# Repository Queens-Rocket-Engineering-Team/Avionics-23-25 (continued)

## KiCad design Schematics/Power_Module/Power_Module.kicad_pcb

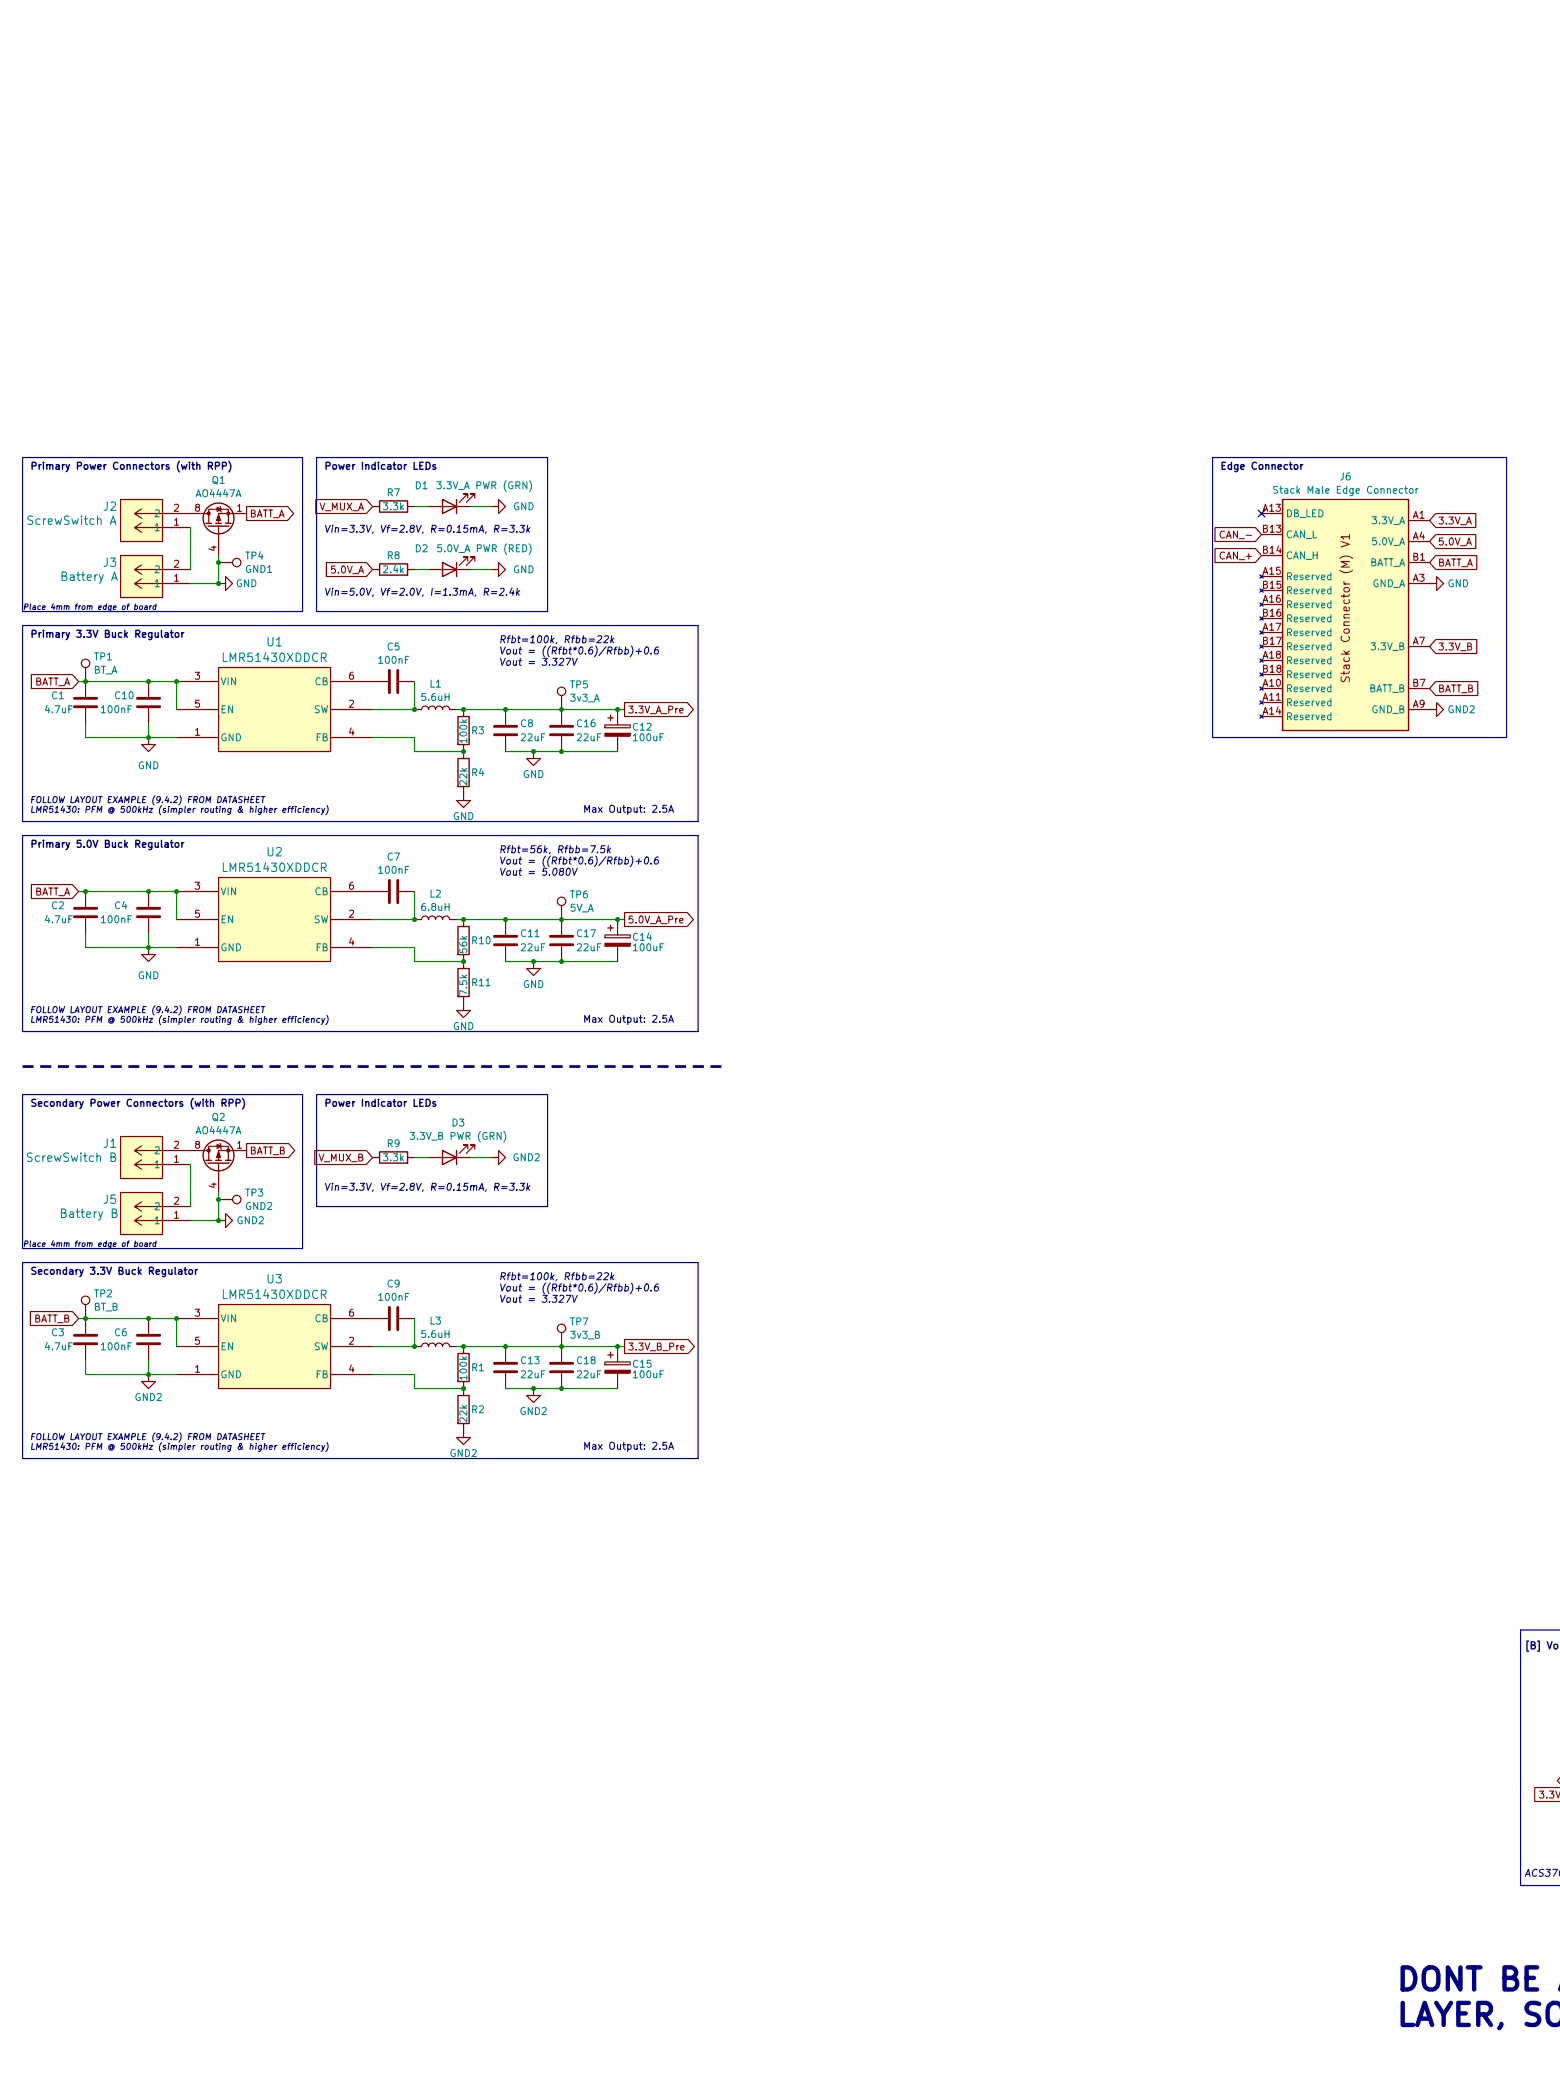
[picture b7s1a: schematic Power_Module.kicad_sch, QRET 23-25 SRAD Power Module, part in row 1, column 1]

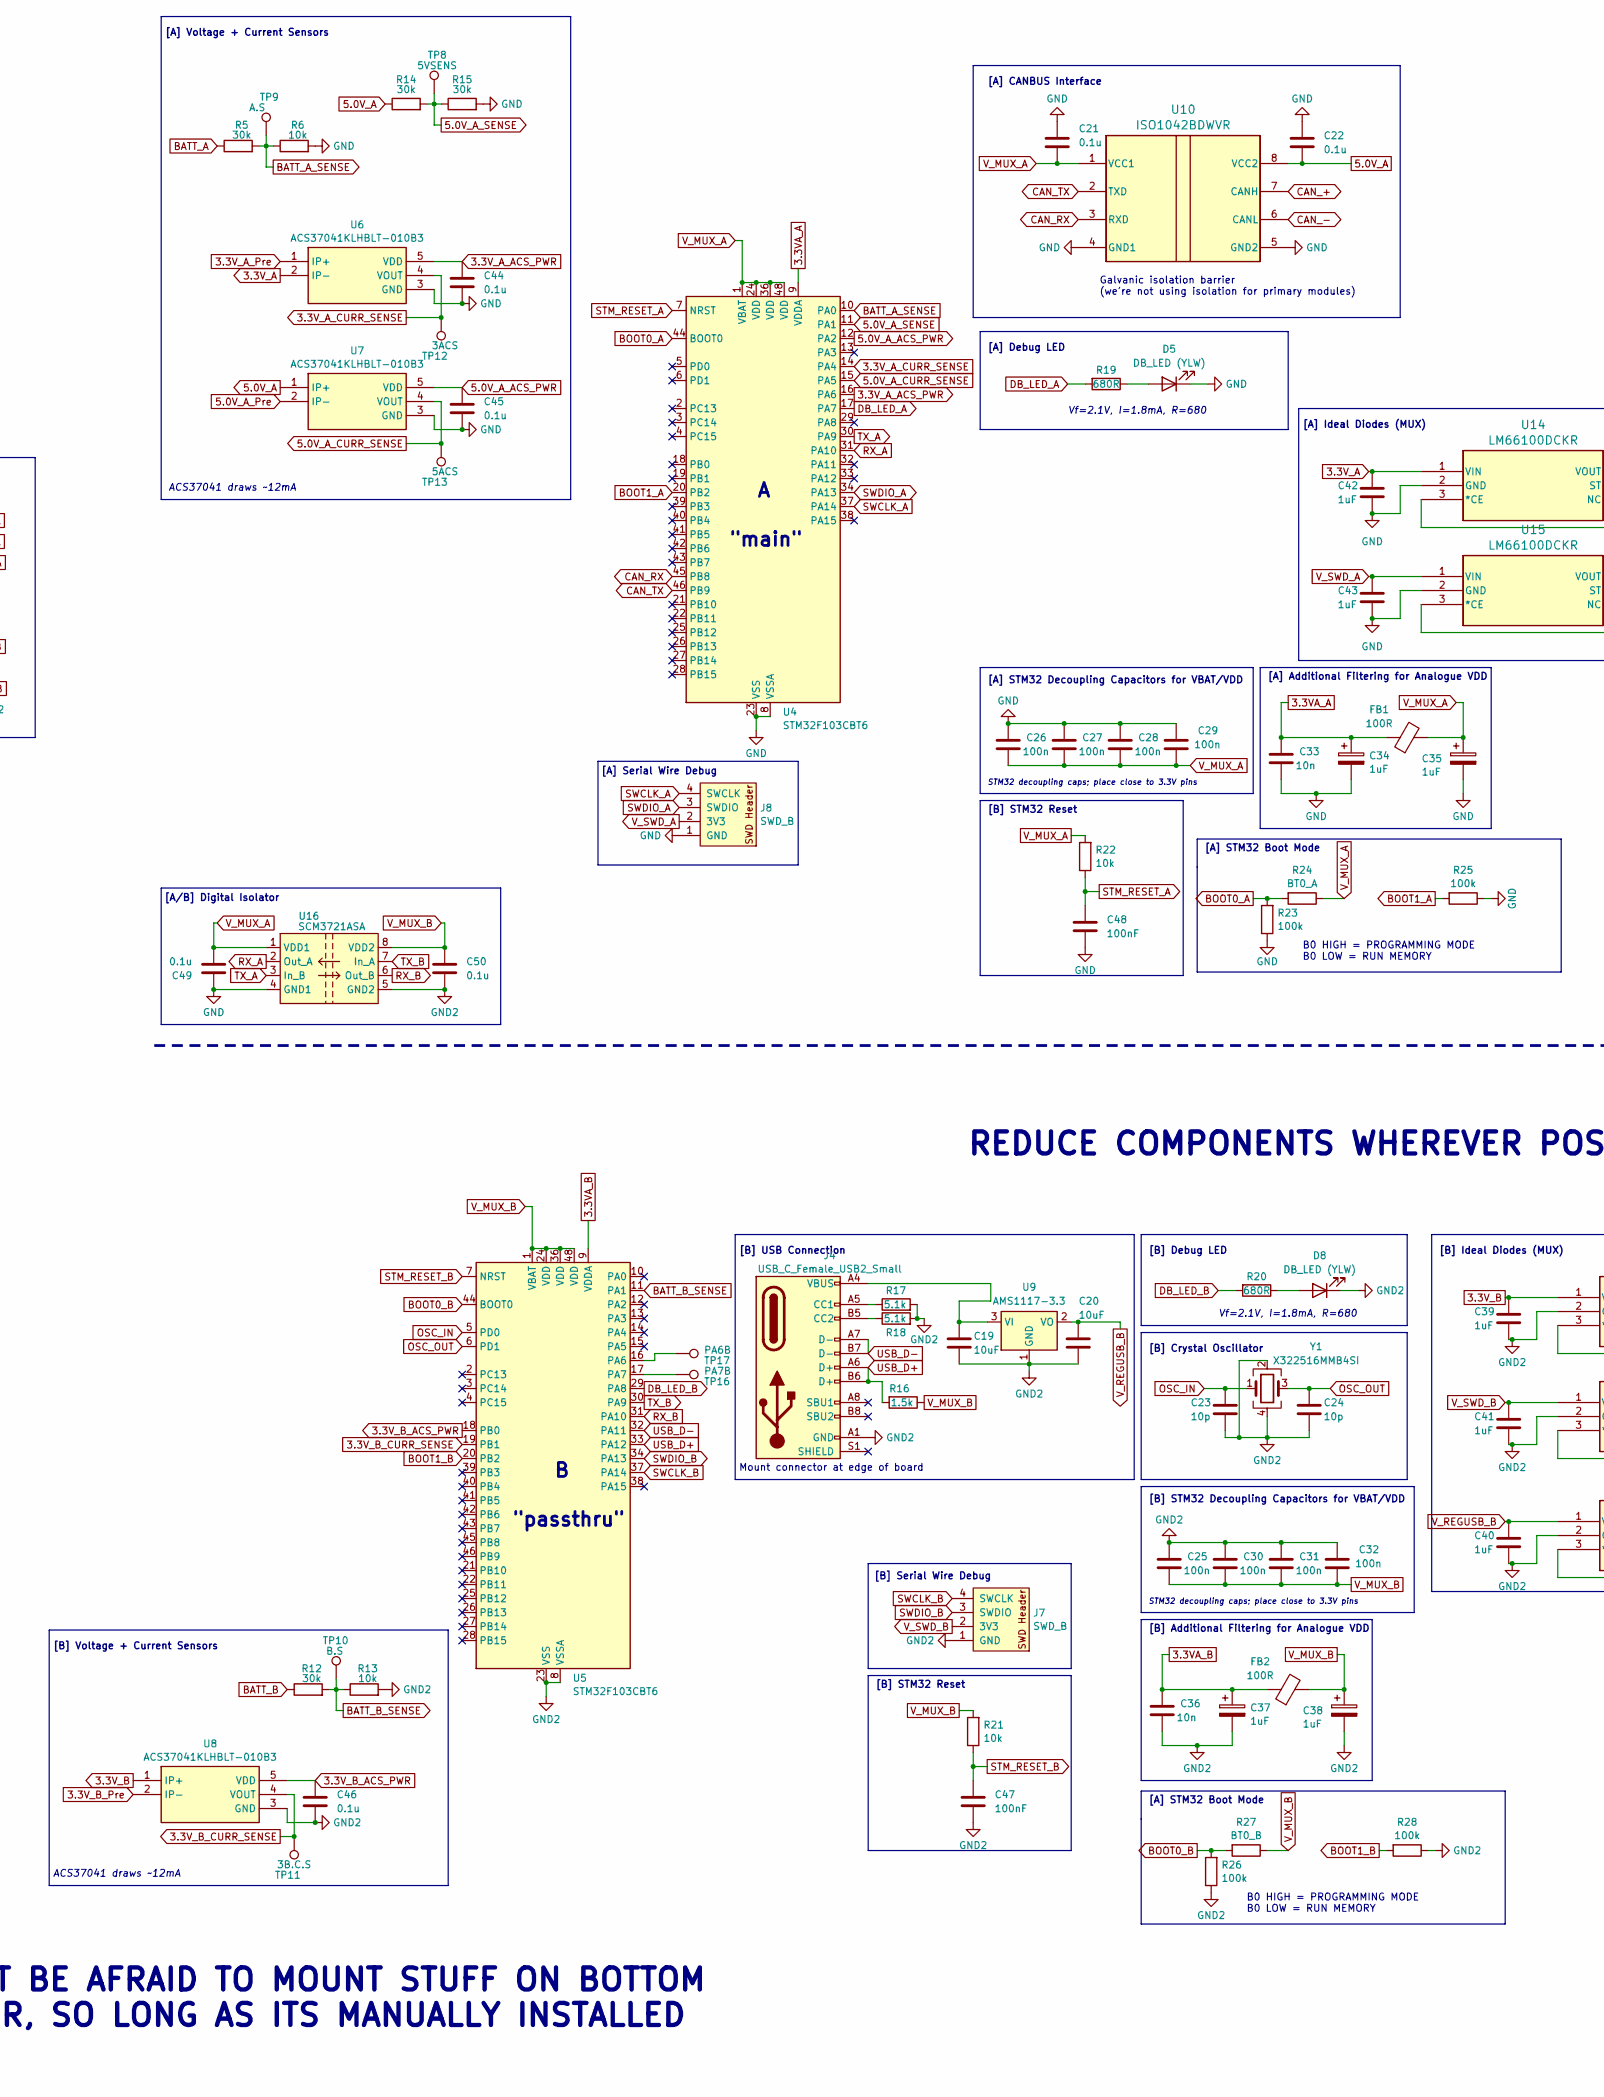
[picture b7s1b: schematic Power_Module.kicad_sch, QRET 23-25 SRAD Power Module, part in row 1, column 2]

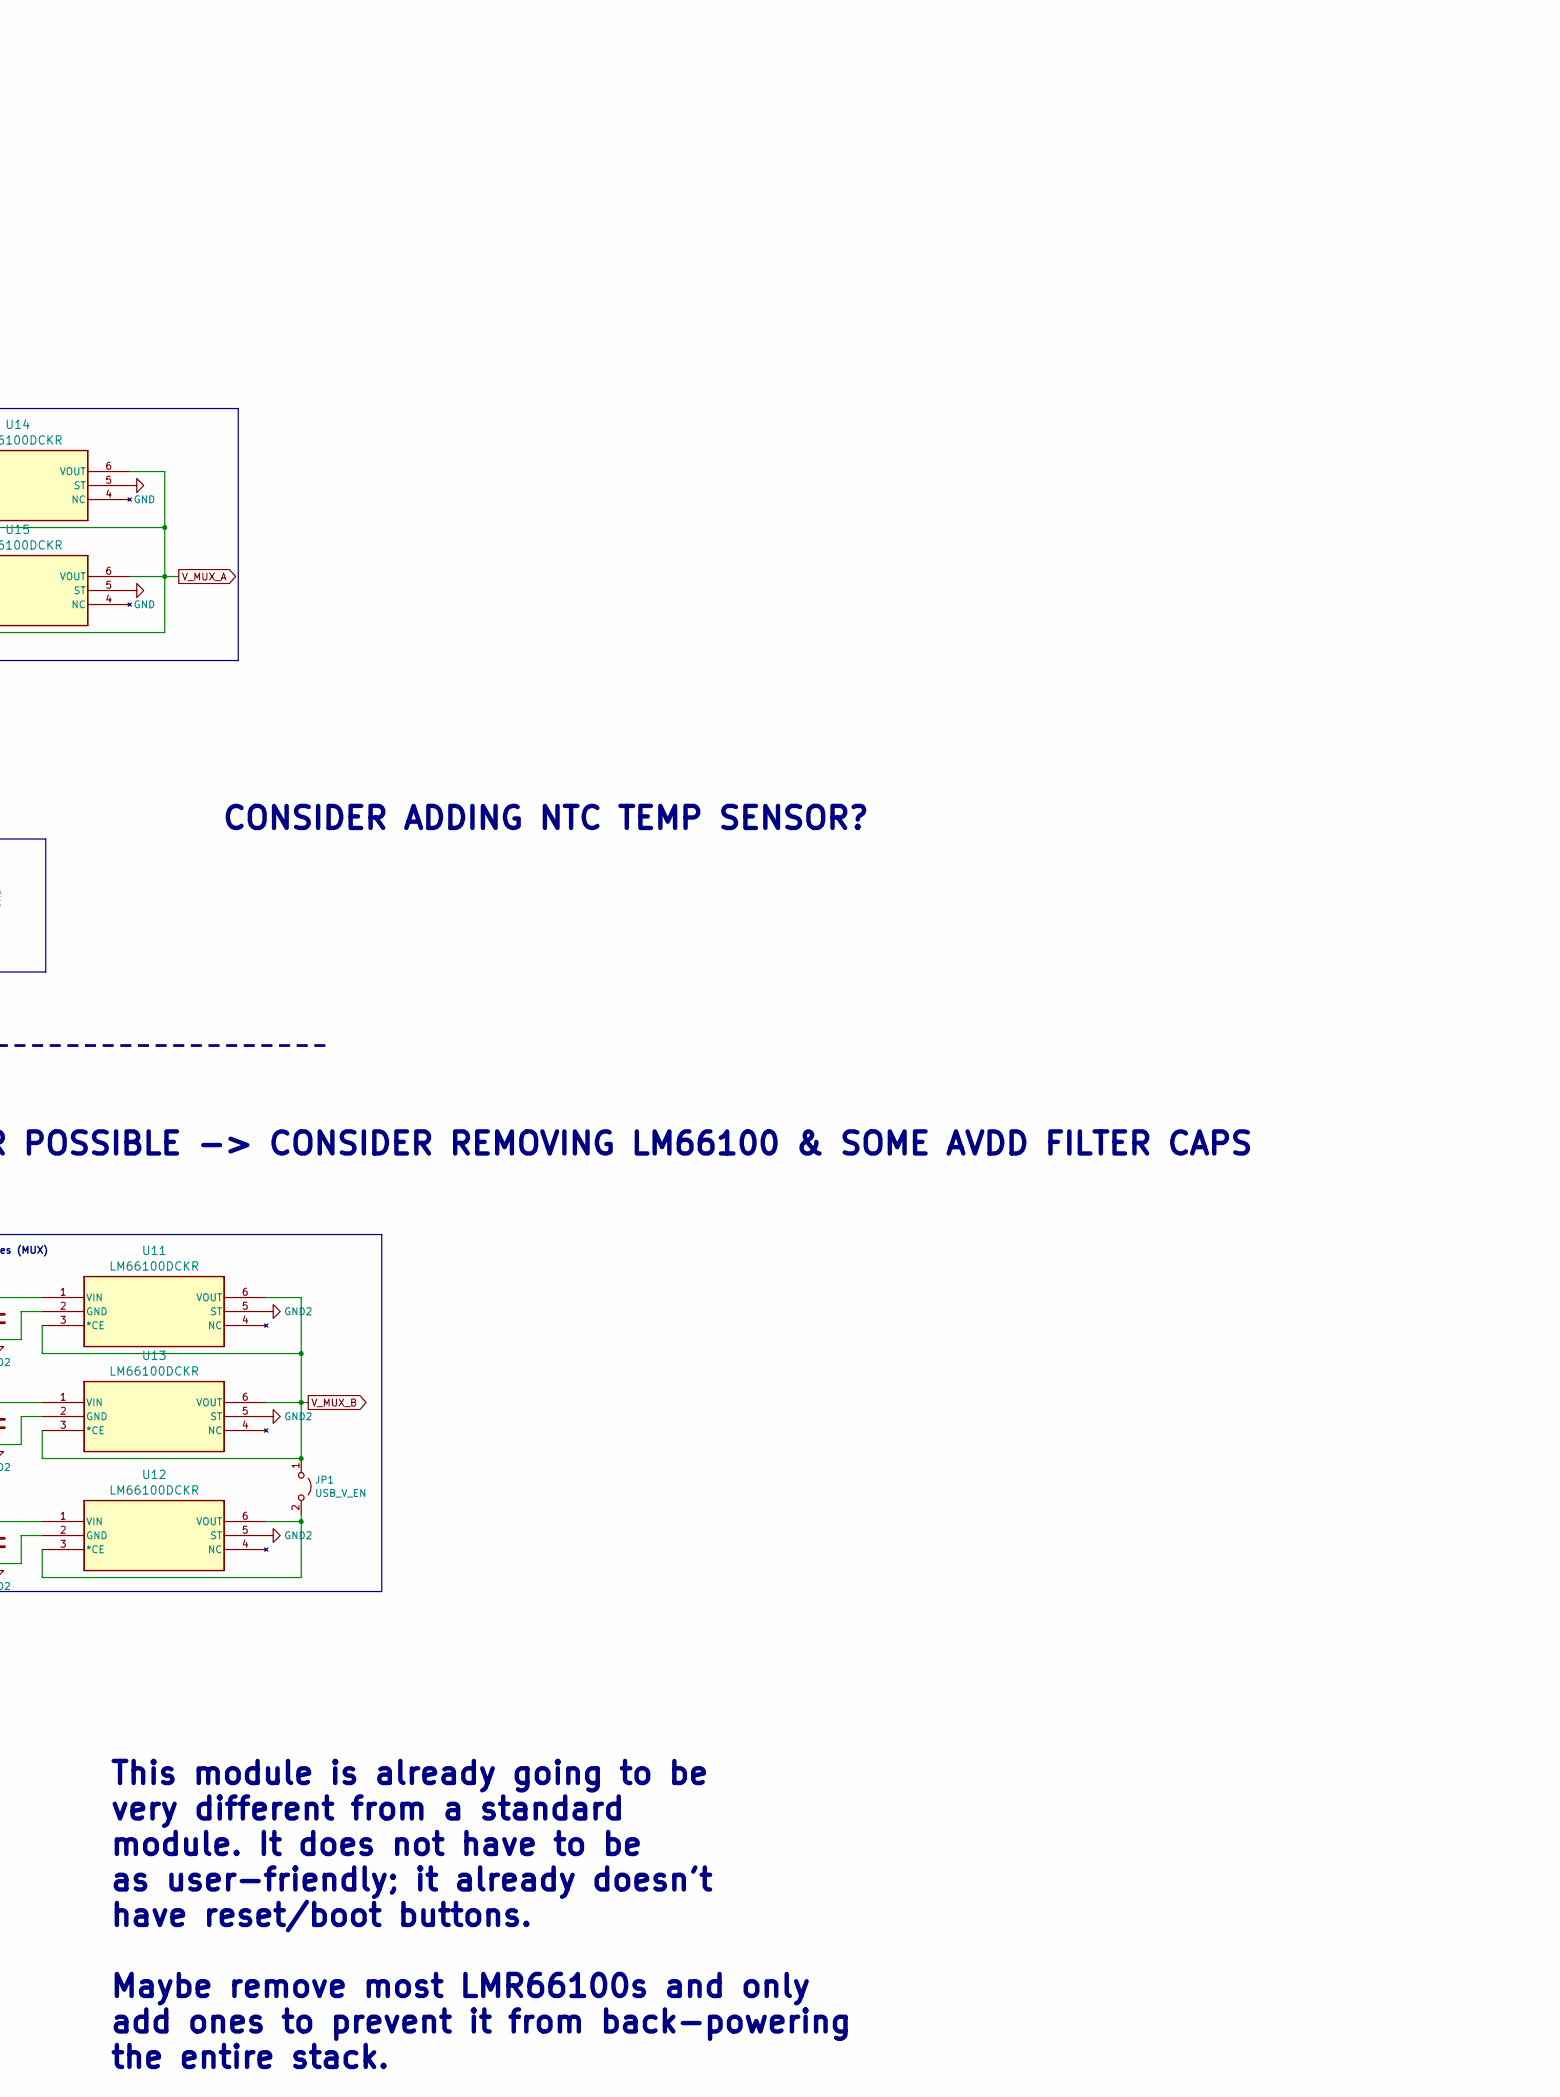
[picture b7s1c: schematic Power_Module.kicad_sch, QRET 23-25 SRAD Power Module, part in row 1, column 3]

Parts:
C1, C2, C3: 4.7uF; C_0805_2012Metric; JLCPCB C1779
C4, C5, C6, C7, C9, C10, C47, C48: 100nF; C_0603_1608Metric; JLCPCB C14663
C8, C11, C13, C16, C17, C18: 22uF; C_0805_2012Metric; JLCPCB C45783
C12, C14, C15: 100uF; CP_Elec_6.3x5.9; Digikey 732-8419-1-ND
C19, C20: 10uF; C_0603_1608Metric; JLCPCB C96446
C21, C22, C44, C45, C46: 0.1u; C_0603_1608Metric; JLCPCB C14663
C23, C24: 10p; C_0603_1608Metric; JLCPCB C1634
C25, C26, C27, C28, C29, C30, C31, C32: 100n; C_0402_1005Metric; JLCPCB C1525
C33, C36: 10n; C_0603_1608Metric; JLCPCB C57112
C34, C35, C37, C38: 1uF; C_0805_2012Metric; JLCPCB C28323
C39, C40, C41, C42, C43: 1uF; C_0603_1608Metric; JLCPCB C15849
C49, C50: 0.1u; C_0603_1608Metric_Pad1.08x0.95mm_HandSolder; JLCPCB C14663
D1: 3.3V_A PWR (GRN); LED_0805_2012Metric; JLCPCB C2297
D2: 5.0V_A PWR (RED); LED_0805_2012Metric; JLCPCB C84256
D3: 3.3V_B PWR (GRN); LED_0805_2012Metric; JLCPCB C2297
D5, D8: DB_LED (YLW); LED_0603_1608Metric; JLCPCB C72038
FB1, FB2: 100R; R_0805_2012Metric; JLCPCB C1015
J1: ScrewSwitch B; CONN_2-1445057-2_TYCO; Digikey A33212CT-ND
J2: ScrewSwitch A; CONN_2-1445057-2_TYCO; Digikey A33212CT-ND
J3: Battery A; CONN_2-1445057-2_TYCO; Digikey A33212CT-ND
J4: USB_C_Female_USB2_Small; USB_C_DB-108PWB; JLCPCB C2936184
J5: Battery B; CONN_2-1445057-2_TYCO; Digikey A33212CT-ND
J6: Stack Male Edge Connector; BUS_PCIexpress_x1
J7, J8: SWD_B; SWD_PinHeader_1x04_P2.54mm_Horizontal_SMD; Digikey 952-3233-ND
JP1: USB_V_EN; SolderJumper-2_P1.3mm_Open_RoundedPad1.0x1.5mm
L1, L3: 5.6uH; L_Bourns_SRN8040TA; Digikey SDCHA1V8040-5R6-R
L2: 6.8uH; L_Bourns_SRN8040TA; Digikey HPC 8040NC-6R8M
Q1, Q2: AO4447A; SOIC-8_3.9x4.9mm_P1.27mm; JLCPCB C125867
R1, R3, R23, R25, R26, R28: 100k; R_0603_1608Metric; JLCPCB C25803
R2, R4: 22k; R_0603_1608Metric; JLCPCB C31850
R5, R12, R14, R15: 30k; R_0603_1608Metric; JLCPCB C22984
R6, R13, R21, R22: 10k; R_0603_1608Metric; JLCPCB C25804
R7, R9: 3.3k; R_0603_1608Metric; JLCPCB C22978
R8: 2.4k; R_0603_1608Metric; JLCPCB C22940
R10: 56k; R_0603_1608Metric; JLCPCB C23206
R11: 7.5k; R_0603_1608Metric; JLCPCB C23234
R16: 1.5k; R_0603_1608Metric; JLCPCB C22843
R17, R18: 5.1k; R_0603_1608Metric; JLCPCB C23186
R19, R20: 680R; R_0603_1608Metric; JLCPCB C23228
R24: BT0_A; R_0603_1608Metric_Pad0.98x0.95mm_HandSolder
R27: BT0_B; R_0603_1608Metric_Pad0.98x0.95mm_HandSolder
TP1: BT_A; TestPoint_Pad_2.0x2.0mm
TP2: BT_B; TestPoint_Pad_2.0x2.0mm
TP3: GND2; TestPoint_Pad_2.0x2.0mm
TP4: GND1; TestPoint_Pad_2.0x2.0mm
TP5: 3v3_A; TestPoint_Pad_2.0x2.0mm
TP6: 5V_A; TestPoint_Pad_2.0x2.0mm
TP7: 3v3_B; TestPoint_Pad_2.0x2.0mm
TP8: 5VSENS; TestPoint_Pad_1.5x1.5mm
TP9: A.S; TestPoint_Pad_1.5x1.5mm
TP10: B.S; TestPoint_Pad_1.5x1.5mm
TP11: 3B.C.S; TestPoint_Pad_1.5x1.5mm
TP12: 3ACS; TestPoint_Pad_1.5x1.5mm
TP13: 5ACS; TestPoint_Pad_1.5x1.5mm
TP16: PA7B; TestPoint_Pad_1.5x1.5mm
TP17: PA6B; TestPoint_Pad_1.5x1.5mm
U1, U2, U3: LMR51430XDDCR; SOT-23-6_Handsoldering; Digikey 296-LMR51430XDDCRCT-ND
U4, U5: STM32F103CBT6; LQFP-48_7x7mm_P0.5mm; JLCPCB C8304
U6, U7, U8: ACS37041KLHBLT-010B3; APS12628LLHALTBAP_HandSolder; Digikey 620-ACS37041KLHBLT-010B3CT-ND
U9: AMS1117-3.3; SOT-223-3_TabPin2; JLCPCB C6186
U10: ISO1042BDWVR; SOIC-8 ISO1042BDWV; JLCPCB C484409
U11, U12, U13, U14, U15: LM66100DCKR; SC-70-6_Handsoldering; JLCPCB C2869734
U16: SCM3721ASA; SOIC-8_3.9x4.9mm_P1.27mm; Digikey 2725-SCM3721ASACT-ND
Y1: X322516MMB4SI; Crystal_SMD_3225-4Pin_3.2x2.5mm; JLCPCB C13738

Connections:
3.3VA_A: C33.1, C34.1, FB1.1, U4.9 (VDDA)
3.3VA_B: C36.1, C37.1, FB2.1, U5.9 (VDDA)
3.3V_A: C42.1, J6.A1 (3.3V_A), J6.A2 (3.3V_A), U6.2 (IP-), U14.1 (VIN)
3.3V_A_ACS_PWR: C44.1, U4.16 (PA6), U6.5 (VDD)
3.3V_A_CURR_SENSE: TP12.1, U4.14 (PA4), U6.4 (VOUT)
3.3V_A_Pre: C8.1, C12.1, C16.1, L1.2, R3.1, TP5.1, U6.1 (IP+)
3.3V_B: C39.1, J6.A7 (3.3V_B), J6.A8 (3.3V_B), U8.1 (IP+), U11.1 (VIN)
3.3V_B_ACS_PWR: C46.1, U5.18 (PB0), U8.5 (VDD)
3.3V_B_CURR_SENSE: TP11.1, U5.19 (PB1), U8.4 (VOUT)
3.3V_B_Pre: C13.1, C15.1, C18.1, L3.2, R1.1, TP7.1, U8.2 (IP-)
5.0V_A: C22.2, J6.A4 (5.0V_A), J6.A5 (5.0V_A), R8.1, R14.1, U7.1 (IP+), U10.8 (VCC2)
5.0V_A_ACS_PWR: C45.1, U4.12 (PA2), U7.5 (VDD)
5.0V_A_CURR_SENSE: TP13.1, U4.15 (PA5), U7.4 (VOUT)
5.0V_A_Pre: C11.1, C14.1, C17.1, L2.2, R10.1, TP6.1, U7.2 (IP-)
5.0V_A_SENSE: R14.2, R15.1, TP8.1, U4.11 (PA1)
BATT_A: C1.1, C2.1, C4.1, C10.1, J6.B1 (BATT_A), J6.B2 (BATT_A), J6.B3 (BATT_A), Q1.1 (S), Q1.2 (S), Q1.3 (S), R5.1, TP1.1, U1.3 (VIN), U1.5 (EN), U2.3 (VIN), U2.5 (EN)
BATT_A_SENSE: R5.2, R6.1, TP9.1, U4.10 (PA0)
BATT_B: C3.1, C6.1, J6.B7 (BATT_B), J6.B8 (BATT_B), J6.B9 (BATT_B), Q2.1 (S), Q2.2 (S), Q2.3 (S), R12.1, TP2.1, U3.3 (VIN), U3.5 (EN)
BATT_B_SENSE: R12.2, R13.1, TP10.1, U5.11 (PA1)
BOOT0_A: R23.2, R24.2, U4.44 (BOOT0)
BOOT0_B: R26.2, R27.2, U5.44 (BOOT0)
BOOT1_A: R25.2, U4.20 (PB2)
BOOT1_B: R28.2, U5.20 (PB2)
CAN_+: J6.B14 (CAN_H), U10.7 (CANH)
CAN_-: J6.B13 (CAN_L), U10.6 (CANL)
CAN_RX: U4.45 (PB8), U10.3 (RXD)
CAN_TX: U4.46 (PB9), U10.2 (TXD)
DB_LED_A: R19.2, U4.17 (PA7)
DB_LED_B: R20.2, U5.29 (PA8)
GND: C1.2, C2.2, C4.2, C8.2, C10.2, C11.2, C12.2, C14.2, C16.2, C17.2, C21.1, C22.1, C26.1, C27.1, C28.1, C29.1, C33.2, C34.2, C35.2, C42.2, C43.2, C44.2, C45.2, C48.2, C49.1, D1.1 (K), D2.1 (K), D5.1 (K), J3.1, J6.A3 (GND_A), J6.A6 (GND_A), J6.B4 (GND_A), J6.B5 (GND_A), J6.B6 (GND_A), J8.1 (GND), Q1.4 (G), R4.2, R6.2, R11.2, R15.2, R23.1, R25.1, TP4.1, U1.1 (GND), U2.1 (GND), U4.8 (VSSA), U4.23 (VSS), U4.35 (VSS), U4.47 (VSS), U6.3 (GND), U7.3 (GND), U10.4 (GND1), U10.5 (GND2), U14.2 (GND), U14.5 (ST), U15.2 (GND), U15.5 (ST), U16.4 (GND1)
GND2: C3.2, C6.2, C13.2, C15.2, C18.2, C19.2, C20.2, C23.2, C24.2, C25.1, C30.1, C31.1, C32.1, C36.2, C37.2, C38.2, C39.2, C40.2, C41.2, C46.2, C47.2, C50.2, D3.1 (K), D8.1 (K), J4.A1 (GND), J4.A12 (GND), J4.B1 (GND), J4.B12 (GND), J5.1, J6.A9 (GND_B), J6.A12 (GND_B), J6.B10 (GND_B), J6.B11 (GND_B), J6.B12 (GND_B), J7.1 (GND), Q2.4 (G), R2.2, R13.2, R17.2, R18.2, R26.1, R28.1, TP3.1, U3.1 (GND), U5.8 (VSSA), U5.23 (VSS), U5.35 (VSS), U5.47 (VSS), U8.3 (GND), U9.1 (GND), U11.2 (GND), U11.5 (ST), U12.2 (GND), U12.5 (ST), U13.2 (GND), U13.5 (ST), U16.5 (GND2), Y1.2, Y1.4
unnamed: D1.2 (A), R7.2
unnamed: D2.2 (A), R8.2
unnamed: D3.2 (A), R9.2
unnamed: D5.2 (A), R19.1
unnamed: D8.2 (A), R20.1
unnamed: J1.1, J5.2
unnamed: J1.2, Q2.5 (D), Q2.6 (D), Q2.7 (D), Q2.8 (D)
unnamed: J2.1, J3.2
unnamed: J2.2, Q1.5 (D), Q1.6 (D), Q1.7 (D), Q1.8 (D)
unnamed: J4.A5 (CC1), R17.1
unnamed: J4.B5 (CC2), R18.1
unnamed: JP1.2 (B), U12.3 (*CE), U12.6 (VOUT)
unnamed: C5.2, U1.6 (CB)
unnamed: R3.2, R4.1, U1.4 (FB)
unnamed: C5.1, L1.1, U1.2 (SW)
unnamed: C7.2, U2.6 (CB)
unnamed: R10.2, R11.1, U2.4 (FB)
unnamed: C7.1, L2.1, U2.2 (SW)
unnamed: C9.2, U3.6 (CB)
unnamed: R1.2, R2.1, U3.4 (FB)
unnamed: C9.1, L3.1, U3.2 (SW)
unnamed: TP17.1, U5.16 (PA6)
unnamed: TP16.1, U5.17 (PA7)
unnamed: C19.1, J4.A4 (VBUS), J4.A9 (VBUS), J4.B4 (VBUS), J4.B9 (VBUS), U9.3 (VI)
OSC_IN: C23.1, U5.5 (PD0), Y1.1
OSC_OUT: C24.1, U5.6 (PD1), Y1.3
RX_A: U4.31 (PA10), U16.2 (Out_A)
RX_B: U5.31 (PA10), U16.6 (Out_B)
STM_RESET_A: C48.1, R22.1, U4.7 (NRST)
STM_RESET_B: C47.1, R21.1, U5.7 (NRST)
SWCLK_A: J8.4 (SWCLK), U4.37 (PA14)
SWCLK_B: J7.4 (SWCLK), U5.37 (PA14)
SWDIO_A: J8.3 (SWDIO), U4.34 (PA13)
SWDIO_B: J7.3 (SWDIO), U5.34 (PA13)
TX_A: U4.30 (PA9), U16.3 (In_B)
TX_B: U5.30 (PA9), U16.7 (In_A)
USB_D+: J4.A6 (D+), J4.B6 (D+), R16.2, U5.33 (PA12)
USB_D-: J4.A7 (D-), J4.B7 (D-), U5.32 (PA11)
V_MUX_A: C21.2, C26.2, C27.2, C28.2, C29.2, C35.1, C49.2, FB1.2, R7.1, R22.2, R24.1, U4.1 (VBAT), U4.24 (VDD), U4.36 (VDD), U4.48 (VDD), U10.1 (VCC1), U14.3 (*CE), U14.6 (VOUT), U15.3 (*CE), U15.6 (VOUT), U16.1 (VDD1)
V_MUX_B: C25.2, C30.2, C31.2, C32.2, C38.1, C50.1, FB2.2, JP1.1 (A), R9.1, R16.1, R21.2, R27.1, U5.1 (VBAT), U5.24 (VDD), U5.36 (VDD), U5.48 (VDD), U11.3 (*CE), U11.6 (VOUT), U13.3 (*CE), U13.6 (VOUT), U16.8 (VDD2)
V_REGUSB_B: C20.1, C40.1, U9.2 (VO), U12.1 (VIN)
V_SWD_A: C43.1, J8.2 (3V3), U15.1 (VIN)
V_SWD_B: C41.1, J7.2 (3V3), U13.1 (VIN)

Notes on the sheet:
Place 4mm from edge of board
Max Output: 2.5A
Primary Power Connectors (with RPP)
[B] Voltage + Current Sensors
B0 HIGH = PROGRAMMING MODE B0 LOW = RUN MEMORY
STM32 decoupling caps; place close to 3.3V pins
[A] Voltage + Current Sensors
Primary 5.0V Buck Regulator
[B] Debug LED
Primary 3.3V Buck Regulator
Vf=2.1V, I=1.8mA, R=680
"main"
Galvanic isolation barrier (we're not using isolation for primary modules)
[B] Crystal Oscillator
ACS37041 draws ~12mA
[B] STM32 Reset
Secondary Power Connectors (with RPP)
Vin=3.3V, Vf=2.8V, R=0.15mA, R=3.3k
FOLLOW LAYOUT EXAMPLE (9.4.2) FROM DATASHEET LMR51430: PFM @ 500kHz (simpler routing & higher efficiency)
Rfbt=56k, Rfbb=7.5k Vout = ((Rfbt*0.6)/Rfbb)+0.6 Vout = 5.080V
Mount connector at edge of board
Power Indicator LEDs
CONSIDER ADDING NTC TEMP SENSOR?
[B] Ideal Diodes (MUX)
Vin=5.0V, Vf=2.0V, I=1.3mA, R=2.4k
[B] Serial Wire Debug
Rfbt=100k, Rfbb=22k Vout = ((Rfbt*0.6)/Rfbb)+0.6 Vout = 3.327V
[A/B] Digital Isolator
"passthru"
[A] STM32 Boot Mode
[A] CANBUS Interface
[B] Additional Filtering for Analogue VDD
REDUCE COMPONENTS WHEREVER POSSIBLE -> CONSIDER REMOVING LM66100 & SOME AVDD FILTER CAPS
This module is already going to be very different from a standard module. It does not have to be as user-friendly; it already doesn't have reset/boot buttons. Maybe remove most LMR66100s and only add ones to prevent it from back-powering the entire stack.
[B] STM32 Decoupling Capacitors for VBAT/VDD
[A] Additional Filtering for Analogue VDD
Edge Connector
[B] USB Connection
[A] Ideal Diodes (MUX)
Secondary 3.3V Buck Regulator

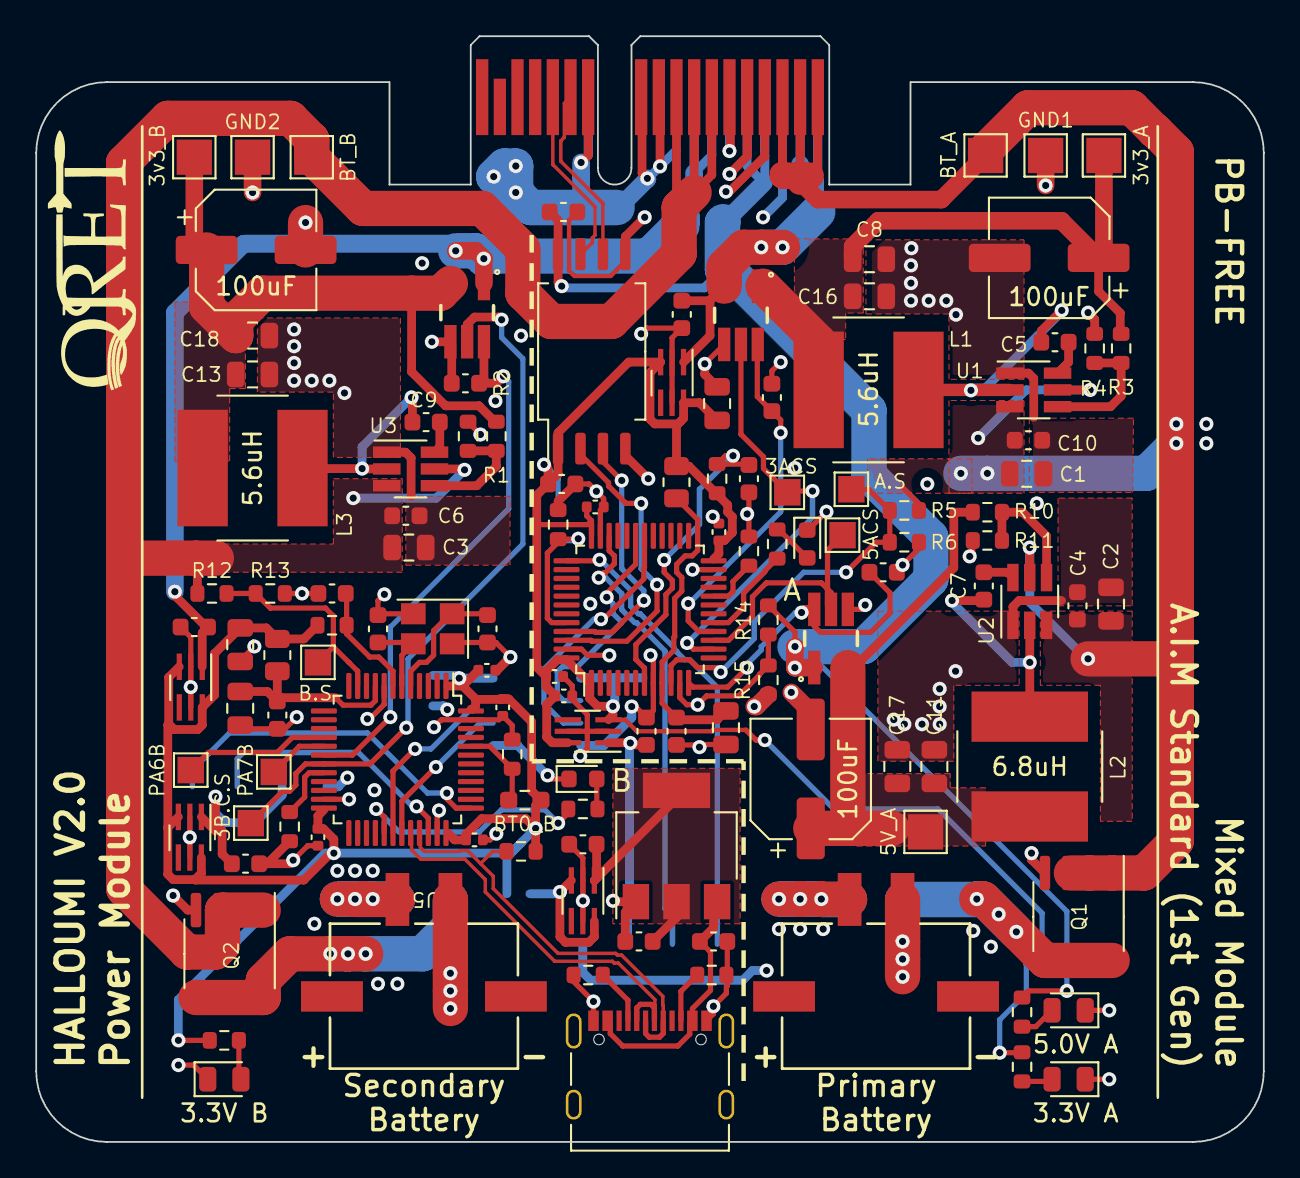
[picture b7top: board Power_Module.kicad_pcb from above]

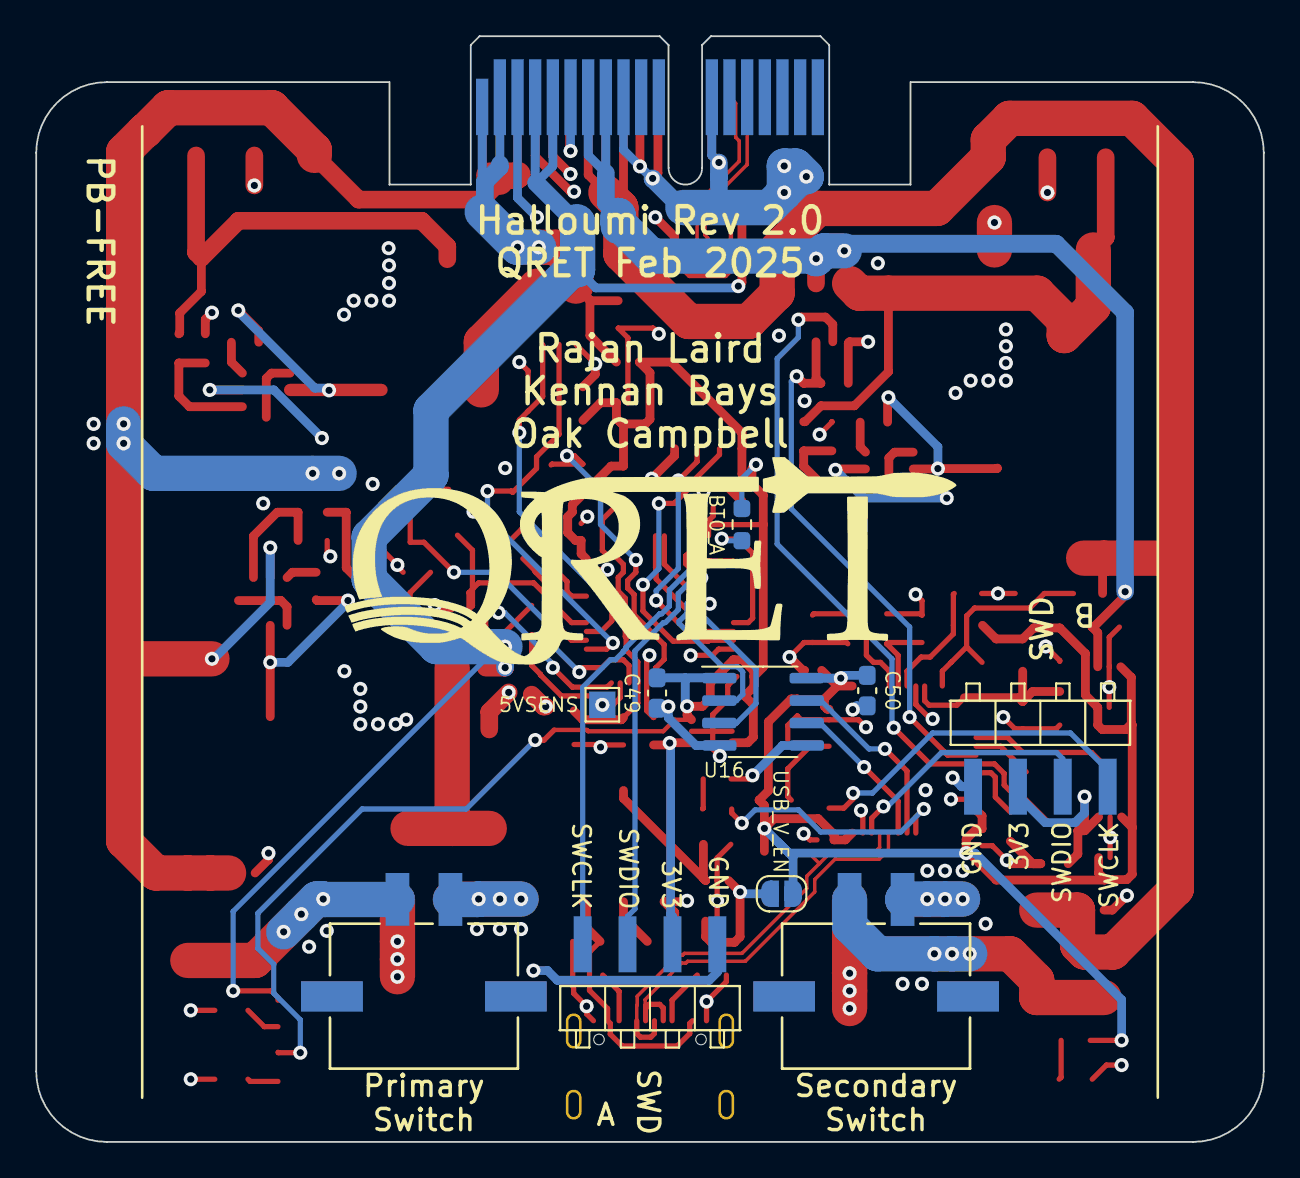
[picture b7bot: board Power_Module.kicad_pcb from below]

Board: 4 copper layers, 69.5 x 62.6 mm, 131 parts (10 on the bottom side), 74 nets.

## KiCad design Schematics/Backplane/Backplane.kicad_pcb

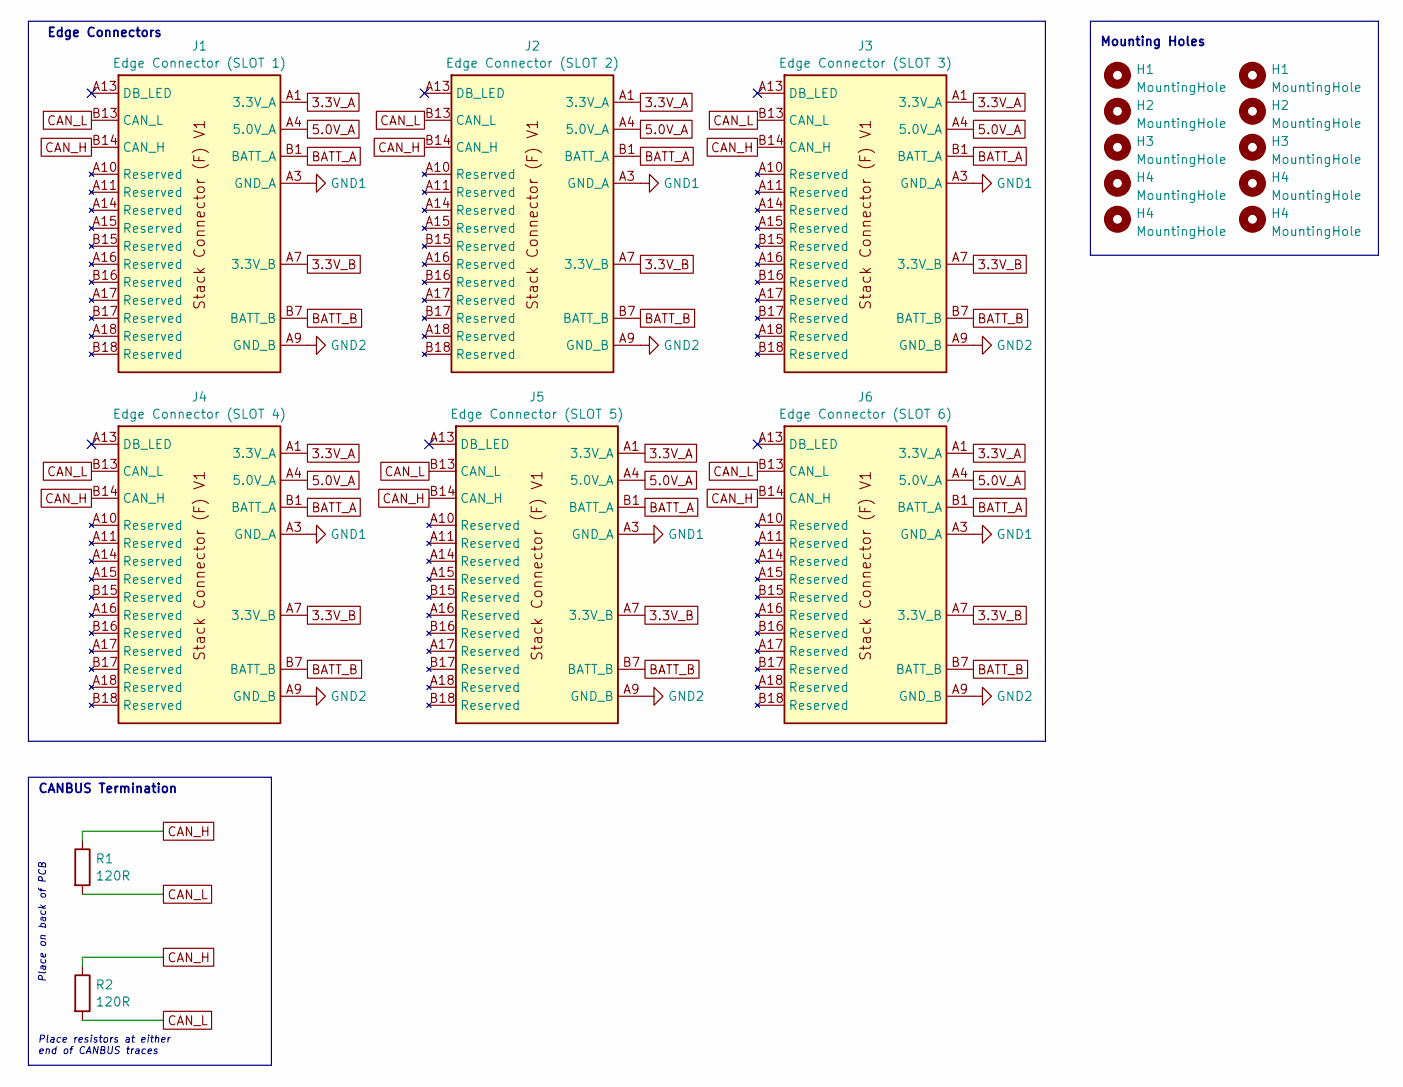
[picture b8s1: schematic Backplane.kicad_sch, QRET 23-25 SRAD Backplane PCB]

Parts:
H1, H2, H3, H4: MountingHole; MountingHole_3.2mm_M3_ISO14580_Pad
J1: Edge Connector (SLOT 1); AMPHENOL_10018784-10210TLF; Digikey 609-2029-ND
J2: Edge Connector (SLOT 2); AMPHENOL_10018784-10210TLF; Digikey 609-2029-ND
J3: Edge Connector (SLOT 3); AMPHENOL_10018784-10210TLF; Digikey 609-2029-ND
J4: Edge Connector (SLOT 4); AMPHENOL_10018784-10210TLF; Digikey 609-2029-ND
J5: Edge Connector (SLOT 5); AMPHENOL_10018784-10210TLF; Digikey 609-2029-ND
J6: Edge Connector (SLOT 6); AMPHENOL_10018784-10210TLF; Digikey 609-2029-ND
R1, R2: 120R; R_0805_2012Metric_Pad1.20x1.40mm_HandSolder; Digikey A129738CT-ND

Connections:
3.3V_A: J1.A1 (3.3V_A), J1.A2 (3.3V_A), J2.A1 (3.3V_A), J2.A2 (3.3V_A), J3.A1 (3.3V_A), J3.A2 (3.3V_A), J4.A1 (3.3V_A), J4.A2 (3.3V_A), J5.A1 (3.3V_A), J5.A2 (3.3V_A), J6.A1 (3.3V_A), J6.A2 (3.3V_A)
3.3V_B: J1.A7 (3.3V_B), J1.A8 (3.3V_B), J2.A7 (3.3V_B), J2.A8 (3.3V_B), J3.A7 (3.3V_B), J3.A8 (3.3V_B), J4.A7 (3.3V_B), J4.A8 (3.3V_B), J5.A7 (3.3V_B), J5.A8 (3.3V_B), J6.A7 (3.3V_B), J6.A8 (3.3V_B)
5.0V_A: J1.A4 (5.0V_A), J1.A5 (5.0V_A), J2.A4 (5.0V_A), J2.A5 (5.0V_A), J3.A4 (5.0V_A), J3.A5 (5.0V_A), J4.A4 (5.0V_A), J4.A5 (5.0V_A), J5.A4 (5.0V_A), J5.A5 (5.0V_A), J6.A4 (5.0V_A), J6.A5 (5.0V_A)
BATT_A: J1.B1 (BATT_A), J1.B2 (BATT_A), J1.B3 (BATT_A), J2.B1 (BATT_A), J2.B2 (BATT_A), J2.B3 (BATT_A), J3.B1 (BATT_A), J3.B2 (BATT_A), J3.B3 (BATT_A), J4.B1 (BATT_A), J4.B2 (BATT_A), J4.B3 (BATT_A), J5.B1 (BATT_A), J5.B2 (BATT_A), J5.B3 (BATT_A), J6.B1 (BATT_A), J6.B2 (BATT_A), J6.B3 (BATT_A)
BATT_B: J1.B7 (BATT_B), J1.B8 (BATT_B), J1.B9 (BATT_B), J2.B7 (BATT_B), J2.B8 (BATT_B), J2.B9 (BATT_B), J3.B7 (BATT_B), J3.B8 (BATT_B), J3.B9 (BATT_B), J4.B7 (BATT_B), J4.B8 (BATT_B), J4.B9 (BATT_B), J5.B7 (BATT_B), J5.B8 (BATT_B), J5.B9 (BATT_B), J6.B7 (BATT_B), J6.B8 (BATT_B), J6.B9 (BATT_B)
CAN_H: J1.B14 (CAN_H), J2.B14 (CAN_H), J3.B14 (CAN_H), J4.B14 (CAN_H), J5.B14 (CAN_H), J6.B14 (CAN_H), R1.1, R2.1
CAN_L: J1.B13 (CAN_L), J2.B13 (CAN_L), J3.B13 (CAN_L), J4.B13 (CAN_L), J5.B13 (CAN_L), J6.B13 (CAN_L), R1.2, R2.2
GND1: J1.A3 (GND_A), J1.A6 (GND_A), J1.B4 (GND_A), J1.B5 (GND_A), J1.B6 (GND_A), J2.A3 (GND_A), J2.A6 (GND_A), J2.B4 (GND_A), J2.B5 (GND_A), J2.B6 (GND_A), J3.A3 (GND_A), J3.A6 (GND_A), J3.B4 (GND_A), J3.B5 (GND_A), J3.B6 (GND_A), J4.A3 (GND_A), J4.A6 (GND_A), J4.B4 (GND_A), J4.B5 (GND_A), J4.B6 (GND_A), J5.A3 (GND_A), J5.A6 (GND_A), J5.B4 (GND_A), J5.B5 (GND_A), J5.B6 (GND_A), J6.A3 (GND_A), J6.A6 (GND_A), J6.B4 (GND_A), J6.B5 (GND_A), J6.B6 (GND_A)
GND2: J1.A9 (GND_B), J1.A12 (GND_B), J1.B10 (GND_B), J1.B11 (GND_B), J1.B12 (GND_B), J2.A9 (GND_B), J2.A12 (GND_B), J2.B10 (GND_B), J2.B11 (GND_B), J2.B12 (GND_B), J3.A9 (GND_B), J3.A12 (GND_B), J3.B10 (GND_B), J3.B11 (GND_B), J3.B12 (GND_B), J4.A9 (GND_B), J4.A12 (GND_B), J4.B10 (GND_B), J4.B11 (GND_B), J4.B12 (GND_B), J5.A9 (GND_B), J5.A12 (GND_B), J5.B10 (GND_B), J5.B11 (GND_B), J5.B12 (GND_B), J6.A9 (GND_B), J6.A12 (GND_B), J6.B10 (GND_B), J6.B11 (GND_B), J6.B12 (GND_B)

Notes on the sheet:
CANBUS Termination
Place resistors at either end of CANBUS traces
Mounting Holes
Edge Connectors
Place on back of PCB
